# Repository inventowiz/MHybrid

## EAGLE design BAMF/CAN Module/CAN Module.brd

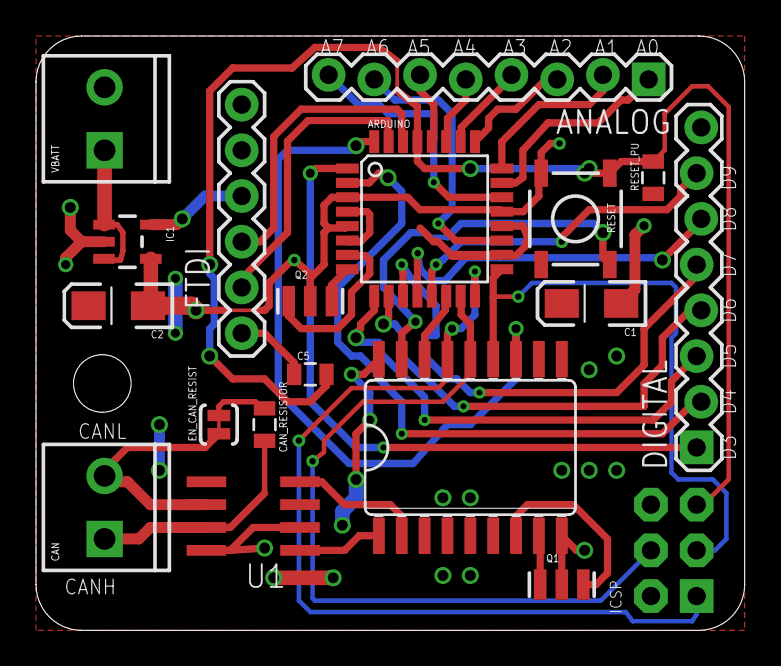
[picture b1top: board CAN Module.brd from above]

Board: 2 copper layers, 39.4 x 33.0 mm, 19 parts (0 on the bottom side), 37 nets.

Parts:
ANALOG: 1X08_LOCK
ARDUINO: TQFP32-08
C1, C2: 220uF; EIA3216-KIT
C5: .1uF; 0805
CAN: M023.5MM; SCREWTERMINAL-3.5MM-2
CAN_RESISTOR: 120; 0805
DIGITAL: 1X08_LOCK
EN_CAN_RESIST: SOLDERJUMPERTRACE; SJ_2S-TRACE
FTDI: FTDI_BASICPTH; FTDI_BASIC
IC1: SOT23-5
J1: AVR_SPI_PRG_6NS; 2X3-NS
Q1, Q2: 16MHz; RESONATOR-SMD
RESET: TACTILE_SWITCH_SMD
RESET_PU: 10k; 0805
U1: MCP2551-SN; SO-08
U$1: MCP2515SO; SO18L
VBATT: M023.5MM; SCREWTERMINAL-3.5MM-2

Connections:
5V: ARDUINO.4, ARDUINO.6, ARDUINO.18, ARDUINO.20, C1.A, C2.A, FTDI.VCC, IC1.5, J1.2, RESET_PU.1, U1.3, U$1.18
A0: ANALOG.1, ARDUINO.23
A1: ANALOG.2, ARDUINO.24
A2: ANALOG.3, ARDUINO.25
A3: ANALOG.4, ARDUINO.26
A4: ANALOG.5, ARDUINO.27
A5: ANALOG.6, ARDUINO.28
A6: ANALOG.7, ARDUINO.19
A7: ANALOG.8, ARDUINO.22
ARD_RX: ARDUINO.30, FTDI.TXO
ARD_TX: ARDUINO.31, FTDI.RXI
CANH: CAN.1, CAN_RESISTOR.2, U1.7
CANL: CAN.2, EN_CAN_RESIST.1, U1.6
CS: ARDUINO.14, U$1.16
D2: ARDUINO.32, U$1.12
D3: ARDUINO.1, DIGITAL.1
D4: ARDUINO.2, DIGITAL.2
D5: ARDUINO.9, DIGITAL.3
D6: ARDUINO.10, DIGITAL.4
D7: ARDUINO.11, DIGITAL.5
D8: ARDUINO.12, DIGITAL.6
D9: ARDUINO.13, DIGITAL.7
GND: ARDUINO.3, ARDUINO.5, ARDUINO.21, C1.C, C2.C, FTDI.GND, IC1.2, IC1.4, J1.6, Q1.2, Q2.2, RESET.3, U1.2, U1.8, U$1.9, VBATT.2
MISO: ARDUINO.16, J1.1, U$1.15
MOSI: ARDUINO.15, J1.4, U$1.14
unnamed: U1.4, U$1.2
unnamed: U1.1, U$1.1
unnamed: CAN_RESISTOR.1, EN_CAN_RESIST.2
unnamed: RESET.2, U$1.17
unnamed: ARDUINO.7, Q2.1
unnamed: ARDUINO.8, Q2.3
unnamed: C5.1, FTDI.DTR
unnamed: Q1.3, U$1.7
unnamed: Q1.1, U$1.8
unnamed: IC1.1, IC1.3, VBATT.1
RESET: ARDUINO.29, C5.2, J1.5, RESET.1, RESET_PU.2
SCK: ARDUINO.17, J1.3, U$1.13

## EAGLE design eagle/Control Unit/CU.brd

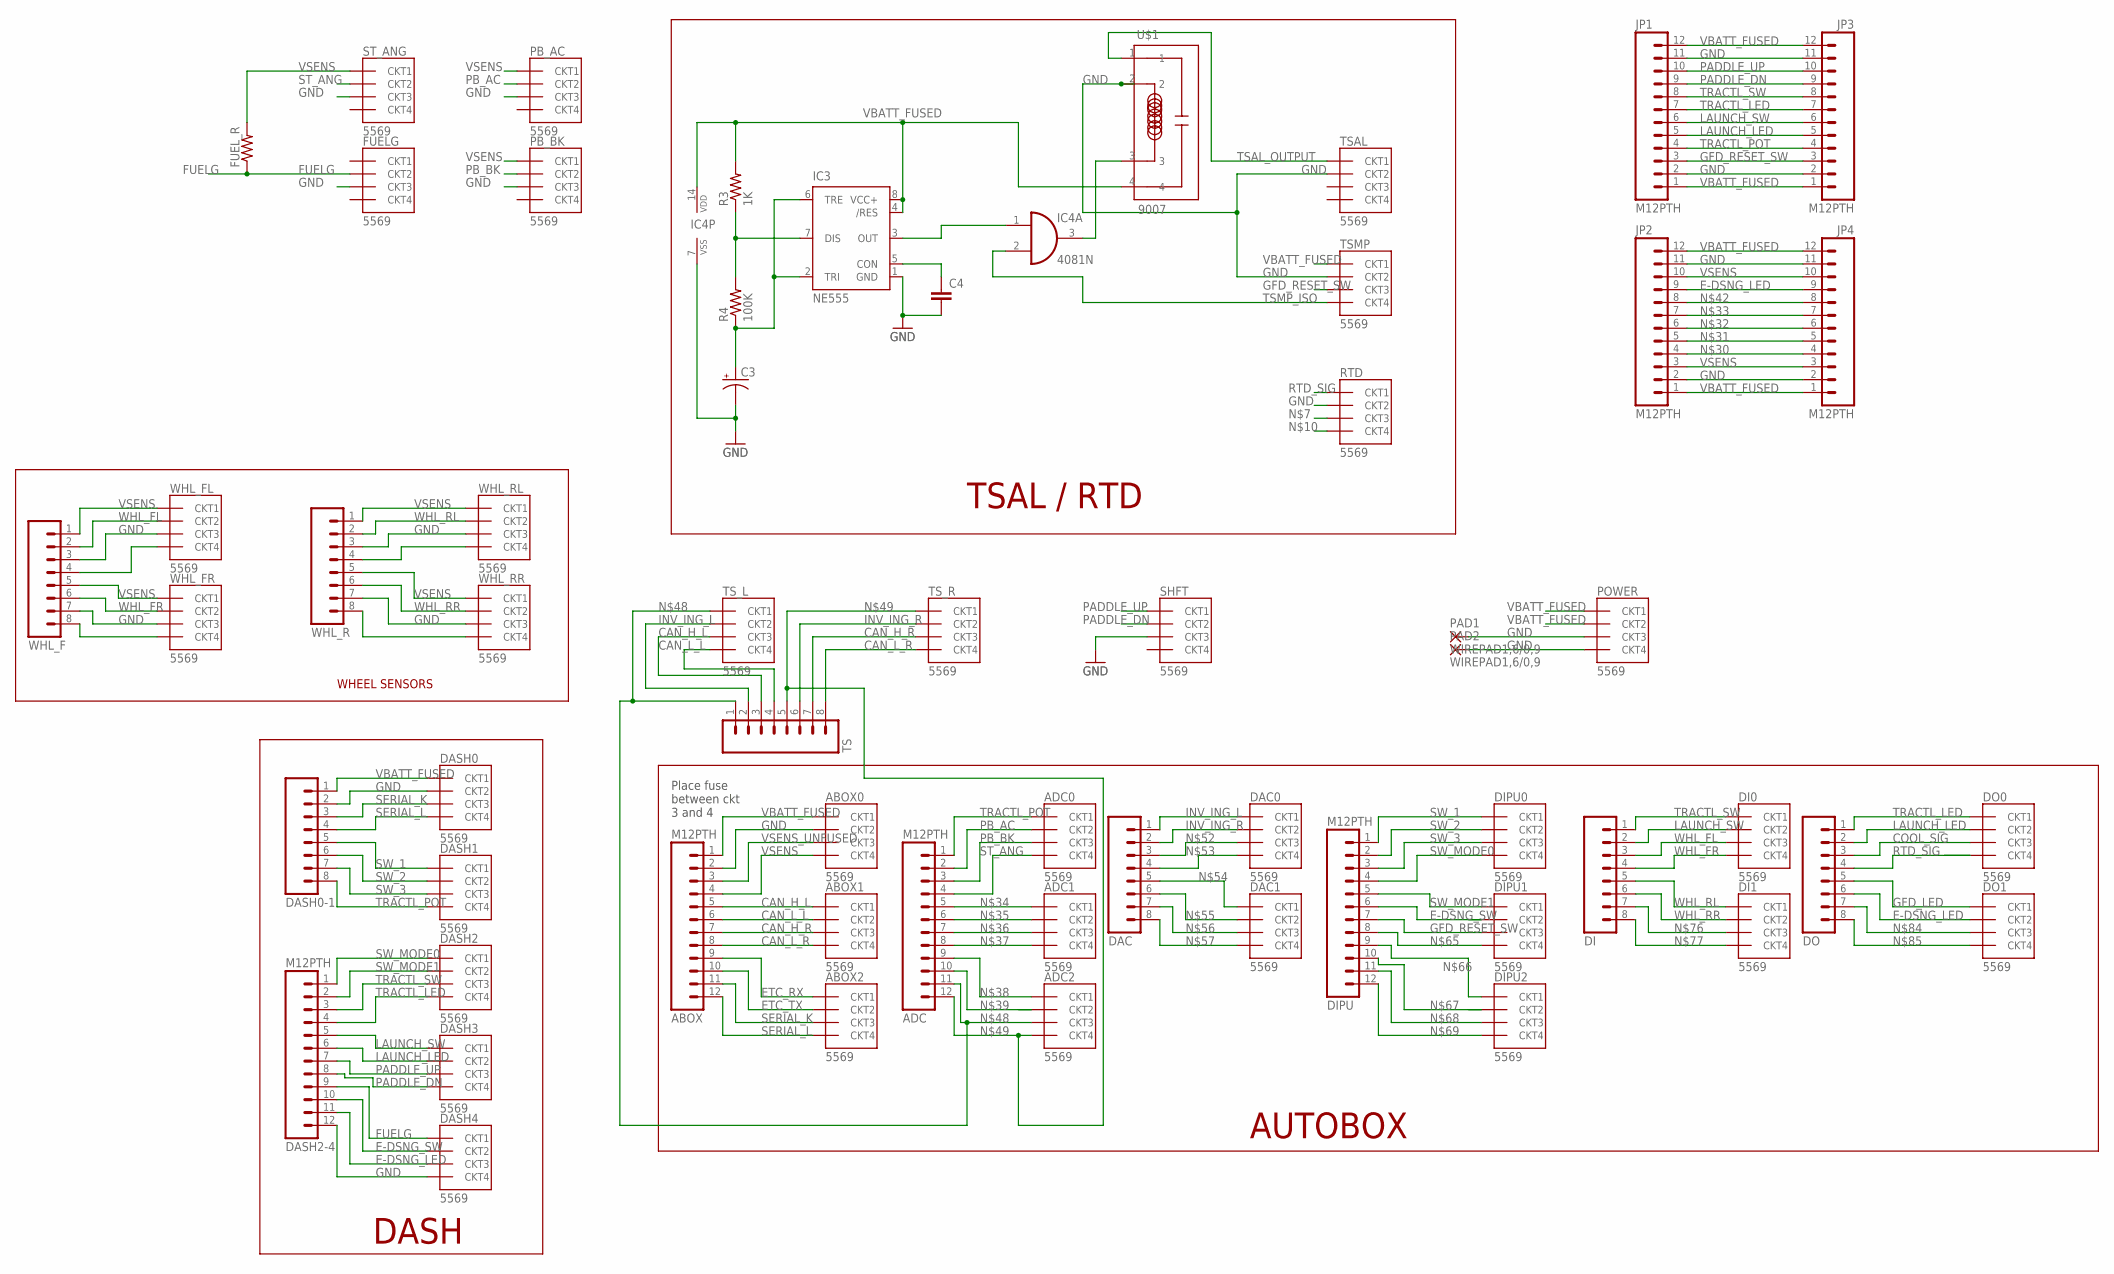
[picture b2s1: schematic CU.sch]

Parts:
ABOX: M12PTH; 1X12
ABOX0, ABOX1, ABOX2: 5569
ADC: M12PTH; 1X12
ADC0, ADC1, ADC2: 5569
C3: CAP_POLPTH1; CPOL-RADIAL-100UF-25V
C4: CAPPTH2; CAP-PTH-SMALL2
DAC: M081X08; 1X08
DAC0, DAC1: 5569
DASH0, DASH1, DASH2, DASH3, DASH4: 5569
DASH0-1: M081X08; 1X08
DASH2-4: M12PTH; 1X12
DI: M081X08; 1X08
DI0, DI1: 5569
DIPU: M12PTH; 1X12
DIPU0, DIPU1, DIPU2: 5569
DO: M081X08; 1X08
DO0, DO1: 5569
FUELG: 5569
FUEL_R: R-US_0204/7; 0204/7
IC3: NE555; DIL-08
IC4: 4081N; DIL14
JP1, JP2, JP3, JP4: M12PTH; 1X12
PAD1, PAD2: WIREPAD1,6/0,9; 1,6/0,9
PB_AC: 5569
PB_BK: 5569
POWER: 5569
R3: 1K; AXIAL-0.3EZ
R4: 100K; AXIAL-0.3EZ
RTD: 5569
SHFT: 5569
ST_ANG: 5569
TS: M081X08; 1X08
TSAL: 5569
TSMP: 5569
TS_L: 5569
TS_R: 5569
U$1: 9007
WHL_F: M081X08; 1X08
WHL_FL: 5569
WHL_FR: 5569
WHL_R: M081X08; 1X08
WHL_RL: 5569
WHL_RR: 5569

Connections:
CAN_H_L: ABOX.5, ABOX1.CKT1, TS.3, TS_L.CKT3
CAN_H_R: ABOX.7, ABOX1.CKT3, TS.7, TS_R.CKT3
CAN_L_L: ABOX.6, ABOX1.CKT2, TS.4, TS_L.CKT4
CAN_L_R: ABOX.8, ABOX1.CKT4, TS.8, TS_R.CKT4
COOL_SIG: DO.3, DO0.CKT3
E-DSNG_LED: DASH2-4.11, DASH4.CKT3, DO.6, DO1.CKT2, JP2.9, JP4.9
E-DSNG_SW: DASH2-4.10, DASH4.CKT2, DIPU.6, DIPU1.CKT2
ETC_RX: ABOX.9, ABOX2.CKT1
ETC_TX: ABOX.10, ABOX2.CKT2
FUELG: DASH2-4.9, DASH4.CKT1, FUELG.CKT2, FUEL_R.1
GFD_LED: DO.5, DO1.CKT1
GFD_RESET_SW: DIPU.7, DIPU1.CKT3, JP1.3, JP3.3, TSMP.CKT3
GND: ABOX.2, ABOX0.CKT2, C3.2 (-), C4.2, DASH0.CKT2, DASH0-1.2, DASH2-4.12, DASH4.CKT4, FUELG.CKT3, IC3.1 (GND), IC4.7 (VSS), JP1.2, JP1.11, JP2.2, JP2.11, JP3.2, JP3.11, JP4.2, JP4.11, PAD1.1, PAD2.1, PB_AC.CKT3, PB_BK.CKT3, POWER.CKT3, POWER.CKT4, RTD.CKT2, SHFT.CKT3, ST_ANG.CKT3, TSAL.CKT2, TSMP.CKT2, U$1.2, WHL_F.3, WHL_F.7, WHL_FL.CKT3, WHL_FR.CKT3, WHL_R.3, WHL_R.7, WHL_RL.CKT3, WHL_RR.CKT3
INV_ING_L: DAC.1, DAC0.CKT1, TS.2, TS_L.CKT2
INV_ING_R: DAC.2, DAC0.CKT2, TS.6, TS_R.CKT2
LAUNCH_LED: DASH2-4.6, DASH3.CKT2, DO.2, DO0.CKT2, JP1.5, JP3.5
LAUNCH_SW: DASH2-4.5, DASH3.CKT1, DI.2, DI0.CKT2, JP1.6, JP3.6
unnamed: WHL_F.4, WHL_FL.CKT4
unnamed: WHL_F.8, WHL_FR.CKT4
unnamed: WHL_R.8, WHL_RR.CKT4
unnamed: IC3.3 (OUT), IC4.1 (I0)
unnamed: WHL_R.4, WHL_RL.CKT4
unnamed: IC4.3 (O), U$1.3
unnamed: IC3.7 (DIS), R3.P$1 (1), R4.P$2 (2)
unnamed: C3.1 (+), IC3.2 (TRI), IC3.6 (TRE), R4.P$1 (1)
unnamed: C4.1, IC3.5 (CON)
unnamed: JP2.4, JP4.4
unnamed: JP2.5, JP4.5
unnamed: JP2.6, JP4.6
unnamed: JP2.7, JP4.7
unnamed: ADC.5, ADC1.CKT1
unnamed: ADC.6, ADC1.CKT2
unnamed: ADC.7, ADC1.CKT3
unnamed: ADC.8, ADC1.CKT4
unnamed: ADC.9, ADC2.CKT1
unnamed: ADC.10, ADC2.CKT2
unnamed: JP2.8, JP4.8
unnamed: ADC.11, ADC2.CKT3, TS.1, TS_L.CKT1
unnamed: ADC.12, ADC2.CKT4, TS.5, TS_R.CKT1
unnamed: DAC.3, DAC0.CKT3
unnamed: DAC.4, DAC0.CKT4
unnamed: DAC.5, DAC1.CKT1
unnamed: DAC.6, DAC1.CKT2
unnamed: DAC.7, DAC1.CKT3
unnamed: DAC.8, DAC1.CKT4
unnamed: DIPU.8, DIPU1.CKT4
unnamed: DIPU.9, DIPU2.CKT1
unnamed: DIPU.10, DIPU2.CKT2
unnamed: DIPU.11, DIPU2.CKT3
unnamed: DIPU.12, DIPU2.CKT4
unnamed: DI.7, DI1.CKT3
unnamed: DI.8, DI1.CKT4
unnamed: DO.7, DO1.CKT3
unnamed: DO.8, DO1.CKT4
PADDLE_DN: DASH2-4.8, DASH3.CKT4, JP1.9, JP3.9, SHFT.CKT2
PADDLE_UP: DASH2-4.7, DASH3.CKT3, JP1.10, JP3.10, SHFT.CKT1
PB_AC: ADC.2, ADC0.CKT2, PB_AC.CKT2
PB_BK: ADC.3, ADC0.CKT3, PB_BK.CKT2
RTD_SIG: DO.4, DO0.CKT4, RTD.CKT1
SERIAL_K: ABOX.11, ABOX2.CKT3, DASH0.CKT3, DASH0-1.3
SERIAL_L: ABOX.12, ABOX2.CKT4, DASH0.CKT4, DASH0-1.4
ST_ANG: ADC.4, ADC0.CKT4, ST_ANG.CKT2
SW_1: DASH0-1.5, DASH1.CKT1, DIPU.1, DIPU0.CKT1
SW_2: DASH0-1.6, DASH1.CKT2, DIPU.2, DIPU0.CKT2
SW_3: DASH0-1.7, DASH1.CKT3, DIPU.3, DIPU0.CKT3
SW_MODE0: DASH2.CKT1, DASH2-4.1, DIPU.4, DIPU0.CKT4
SW_MODE1: DASH2.CKT2, DASH2-4.2, DIPU.5, DIPU1.CKT1
TRACTL_LED: DASH2.CKT4, DASH2-4.4, DO.1, DO0.CKT1, JP1.7, JP3.7
TRACTL_POT: ADC.1, ADC0.CKT1, DASH0-1.8, DASH1.CKT4, JP1.4, JP3.4
TRACTL_SW: DASH2.CKT3, DASH2-4.3, DI.1, DI0.CKT1, JP1.8, JP3.8
TSAL_OUTPUT: TSAL.CKT1, U$1.1
TSMP_ISO: IC4.2 (I1), TSMP.CKT4
VBATT_FUSED: ABOX.1, ABOX0.CKT1, DASH0.CKT1, DASH0-1.1, IC3.4 (/RES), IC3.8 (VCC+), IC4.14 (VDD), JP1.1, JP1.12, JP2.1, JP2.12, JP3.1, JP3.12, JP4.1, JP4.12, POWER.CKT1, POWER.CKT2, R3.P$2 (2), TSMP.CKT1, U$1.4
VSENS: ABOX.4, ABOX0.CKT4, FUEL_R.2, JP2.3, JP2.10, JP4.3, JP4.10, PB_AC.CKT1, PB_BK.CKT1, ST_ANG.CKT1, WHL_F.1, WHL_F.5, WHL_FL.CKT1, WHL_FR.CKT1, WHL_R.1, WHL_R.5, WHL_RL.CKT1, WHL_RR.CKT1
VSENS_UNFUSED: ABOX.3, ABOX0.CKT3
WHL_FL: DI.3, DI0.CKT3, WHL_F.2, WHL_FL.CKT2
WHL_FR: DI.4, DI0.CKT4, WHL_F.6, WHL_FR.CKT2
WHL_RL: DI.5, DI1.CKT1, WHL_R.2, WHL_RL.CKT2
WHL_RR: DI.6, DI1.CKT2, WHL_R.6, WHL_RR.CKT2

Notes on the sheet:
WHEEL SENSORS
TSAL / RTD
AUTOBOX
DASH
Place fuse between ckt 3 and 4

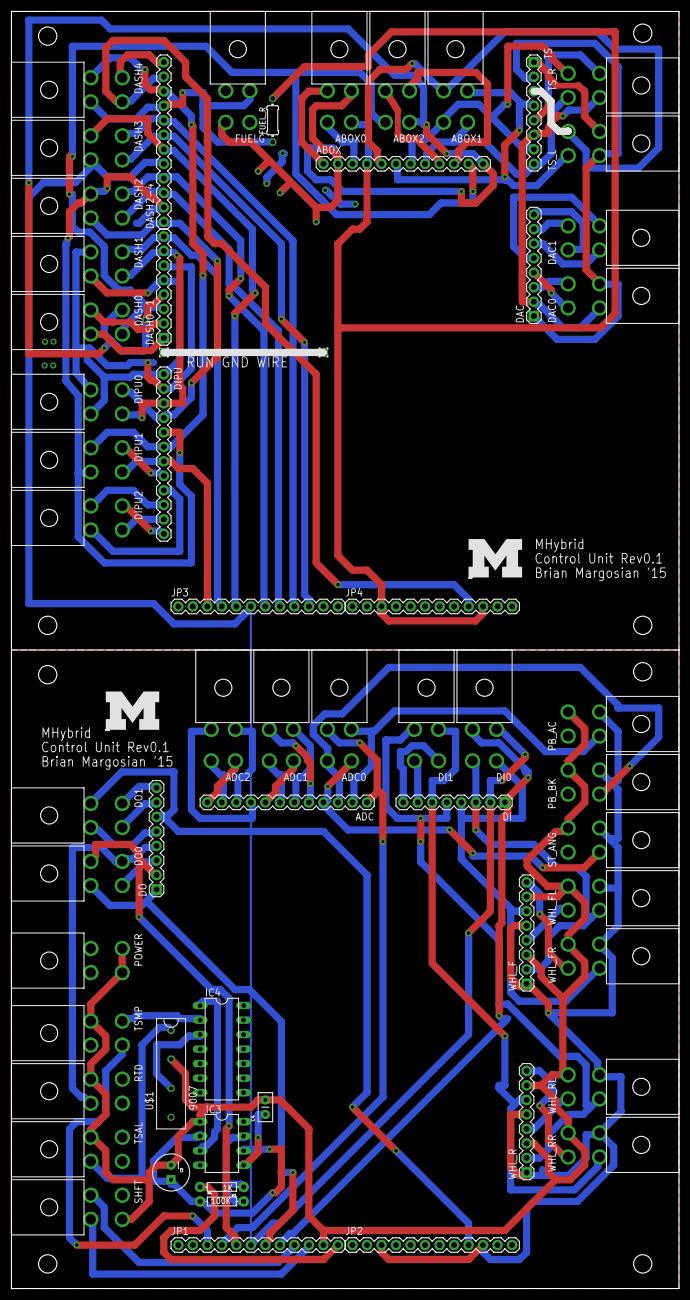
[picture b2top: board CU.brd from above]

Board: 3 copper layers, 116.8 x 223.5 mm, 62 parts (0 on the bottom side), 79 nets.

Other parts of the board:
U$2, U$3: BLOCKM

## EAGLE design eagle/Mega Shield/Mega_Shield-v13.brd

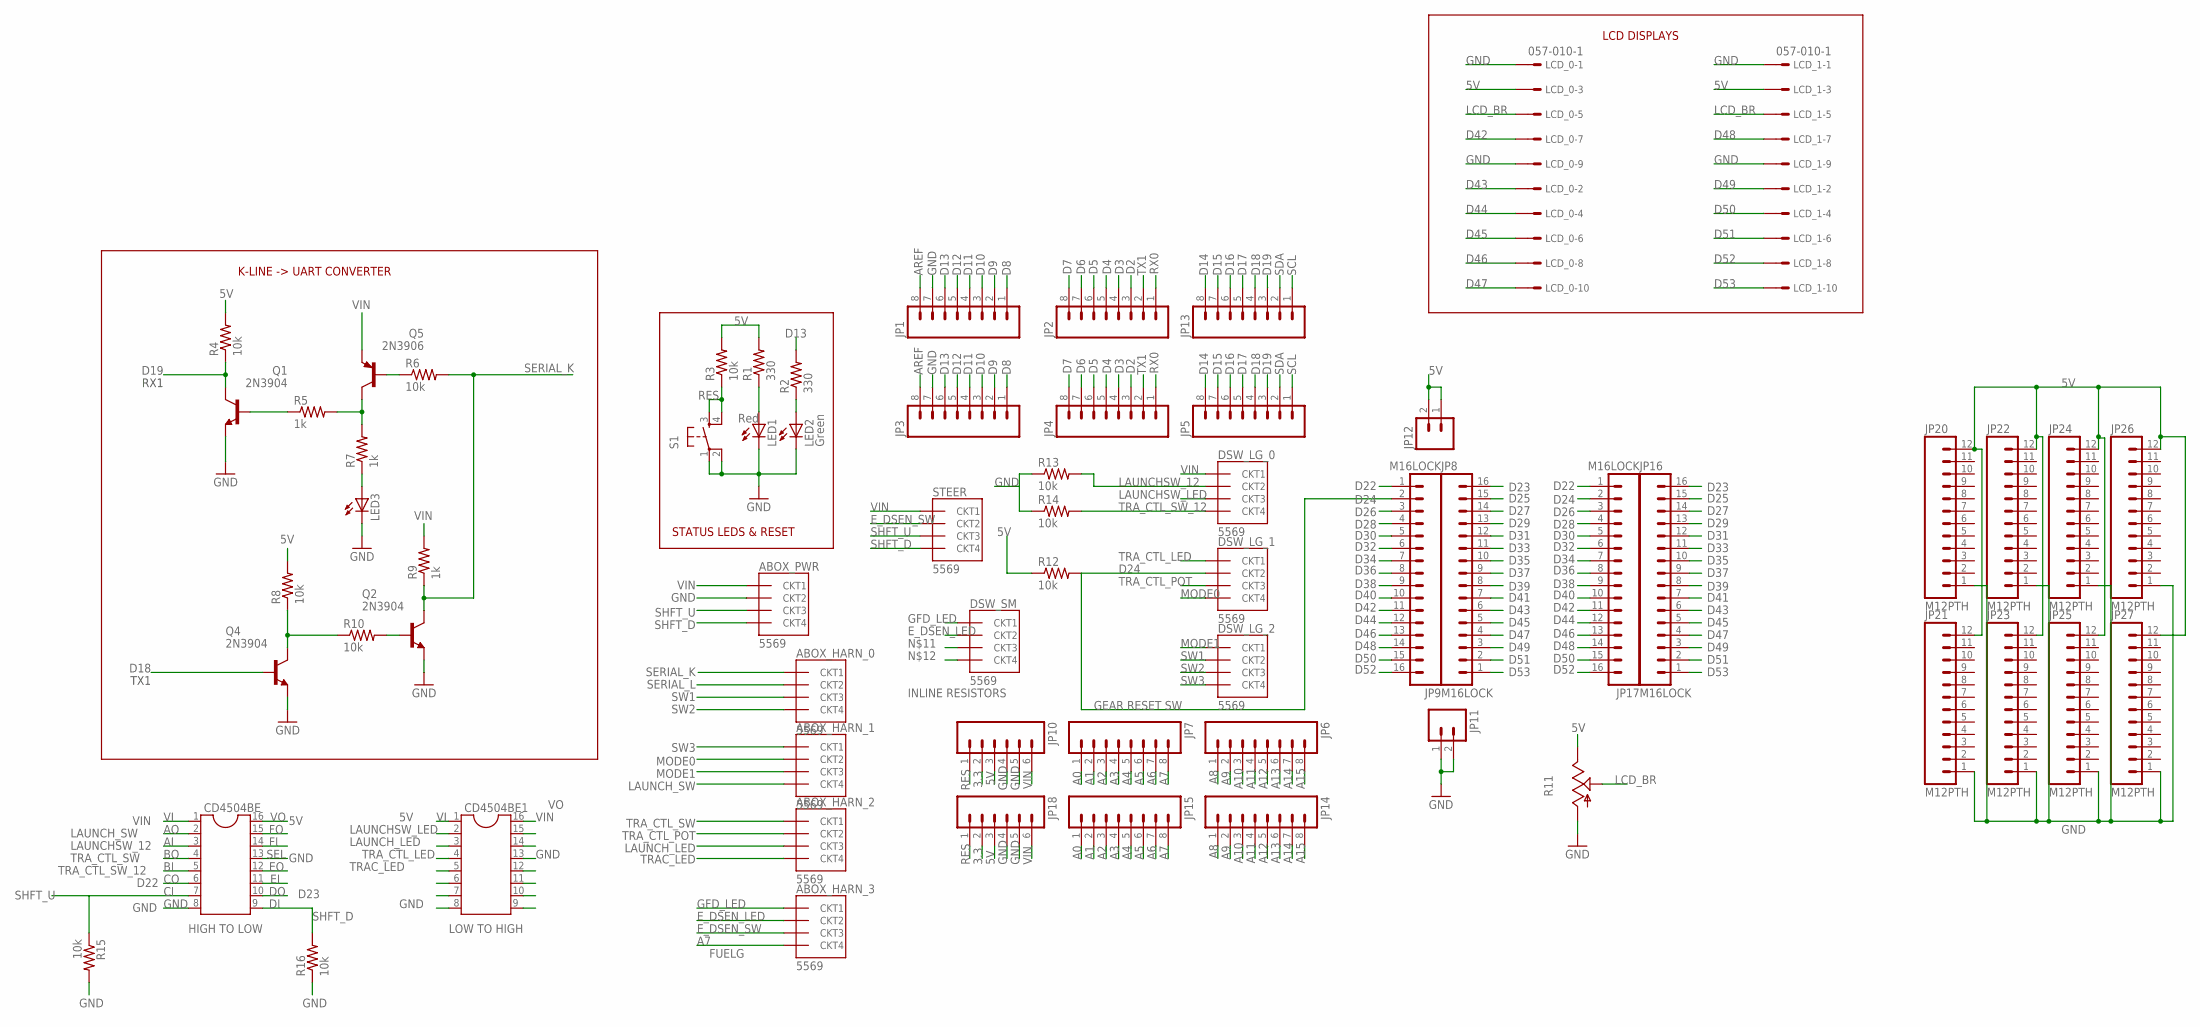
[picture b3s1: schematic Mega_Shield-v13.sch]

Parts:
ABOX_HARN_0, ABOX_HARN_1, ABOX_HARN_2, ABOX_HARN_3: 5569
ABOX_PWR: 5569
CD4504BE, CD4504BE1: DIL16S; SOCKET-16
DSW_LG_0, DSW_LG_1, DSW_LG_2: 5569
DSW_SM: 5569
JP1, JP2, JP3, JP4, JP5, JP6, JP7, JP13, JP14, JP15: M08LOCK; 1X08_LOCK
JP8, JP9, JP16, JP17: M16LOCK; 1X16_LOCK
JP10, JP18: M06LOCK; 1X06_LOCK
JP11, JP12: M02LOCK; 1X02_LOCK
JP20, JP21, JP22, JP23, JP24, JP25, JP26, JP27: M12PTH; 1X12
LCD_0, LCD_1: 057-010-1
LED1: Red; LED5MM
LED2: Green; LED5MM
LED3: LED5MM
Q1, Q2, Q4: 2N3904; TO92
Q5: 2N3906; TO92
R1, R2: 330; AXIAL-0.3
R3: 10k; AXIAL-0.3
R4, R6, R8, R10, R12, R13, R14, R15, R16: 10k; AXIAL-0.3EZ
R5, R7, R9: 1k; AXIAL-0.3EZ
R11: TRIM_US-CT6; CT6
S1: TAC_SWITCHPTH; TACTILE-PTH
STEER: 5569

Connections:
3.3: JP10.2, JP18.2
5V: CD4504BE.16, CD4504BE1.1, JP10.3, JP12.1, JP12.2, JP18.3, JP20.12, JP21.12, JP22.12, JP23.12, JP24.12, JP25.12, JP26.12, JP27.12, LCD_0.3, LCD_1.3, R1.P$2 (2), R3.P$2 (2), R4.P$2 (2), R8.P$2 (2), R11.E, R12.P$1 (1)
A0: JP7.1, JP15.1
A1: JP7.2, JP15.2
A2: JP7.3, JP15.3
A3: JP7.4, JP15.4
A4: JP7.5, JP15.5
A5: JP7.6, JP15.6
A6: JP7.7, JP15.7
A7: ABOX_HARN_3.CKT4, JP7.8, JP15.8
A8: JP6.1, JP14.1
A9: JP6.2, JP14.2
A10: JP6.3, JP14.3
A11: JP6.4, JP14.4
A12: JP6.5, JP14.5
A13: JP6.6, JP14.6
A14: JP6.7, JP14.7
A15: JP6.8, JP14.8
AREF: JP1.8, JP3.8
D2: JP2.3, JP4.3
D3: JP2.4, JP4.4
D4: JP2.5, JP4.5
D5: JP2.6, JP4.6
D6: JP2.7, JP4.7
D7: JP2.8, JP4.8
D8: JP1.1, JP3.1
D9: JP1.2, JP3.2
D10: JP1.3, JP3.3
D11: JP1.4, JP3.4
D12: JP1.5, JP3.5
D13: JP1.6, JP3.6, R2.P$2 (2)
D14: JP5.8, JP13.8
D15: JP5.7, JP13.7
D16: JP5.6, JP13.6
D17: JP5.5, JP13.5
D18: JP5.4, JP13.4, Q4.2 (B)
D19: JP5.3, JP13.3, Q1.1 (C), R4.P$1 (1)
D22: CD4504BE.6, JP9.1, JP17.1
D23: CD4504BE.10, JP8.16, JP16.16
D24: DSW_LG_1.CKT2, JP9.2, JP17.2, R12.P$2 (2)
D25: JP8.15, JP16.15
D26: JP9.3, JP17.3
D27: JP8.14, JP16.14
D28: JP9.4, JP17.4
D29: JP8.13, JP16.13
D30: JP9.5, JP17.5
D31: JP8.12, JP16.12
D32: JP9.6, JP17.6
D33: JP8.11, JP16.11
D34: JP9.7, JP17.7
D35: JP8.10, JP16.10
D36: JP9.8, JP17.8
D37: JP8.9, JP16.9
D38: JP9.9, JP17.9
D39: JP8.8, JP16.8
D40: JP9.10, JP17.10
D41: JP8.7, JP16.7
D42: JP9.11, JP17.11, LCD_0.7
D43: JP8.6, JP16.6, LCD_0.2
D44: JP9.12, JP17.12, LCD_0.4
D45: JP8.5, JP16.5, LCD_0.6
D46: JP9.13, JP17.13, LCD_0.8
D47: JP8.4, JP16.4, LCD_0.10
D48: JP9.14, JP17.14, LCD_1.7
D49: JP8.3, JP16.3, LCD_1.2
D50: JP9.15, JP17.15, LCD_1.4
D51: JP8.2, JP16.2, LCD_1.6
D52: JP9.16, JP17.16, LCD_1.8
D53: JP8.1, JP16.1, LCD_1.10
E_DSEN_LED: ABOX_HARN_3.CKT2, DSW_SM.CKT2
E_DSEN_SW: ABOX_HARN_3.CKT3, STEER.CKT2
GFD_LED: ABOX_HARN_3.CKT1, DSW_SM.CKT1
GND: ABOX_PWR.CKT2, CD4504BE.8, CD4504BE.13, CD4504BE1.8, CD4504BE1.13, JP1.7, JP3.7, JP10.4, JP10.5, JP11.1, JP11.2, JP18.4, JP18.5, JP20.1, JP21.1, JP22.1, JP23.1, JP24.1, JP25.1, JP26.1, JP27.1, LCD_0.1, LCD_0.9, LCD_1.1, LCD_1.9, LED1.K (C), LED2.K (C), LED3.K (C), Q1.3 (E), Q2.3 (E), Q4.3 (E), R11.A, R13.P$1 (1), R14.P$1 (1), R15.P$2 (2), R16.P$1 (1), S1.1, S1.2
LAUNCHSW_12: CD4504BE.3, DSW_LG_0.CKT2, R13.P$2 (2)
LAUNCHSW_LED: CD4504BE1.2, DSW_LG_0.CKT3
LAUNCH_LED: ABOX_HARN_2.CKT3, CD4504BE1.3
LAUNCH_SW: ABOX_HARN_1.CKT4, CD4504BE.2
LCD_BR: LCD_0.5, LCD_1.5, R11.S
MODE0: ABOX_HARN_1.CKT2, DSW_LG_1.CKT4
MODE1: ABOX_HARN_1.CKT3, DSW_LG_2.CKT1
unnamed: Q1.2 (B), R5.P$1 (1)
unnamed: Q5.1 (C), R5.P$2 (2), R7.P$2 (2)
unnamed: Q5.2 (B), R6.P$1 (1)
unnamed: LED3.A, R7.P$1 (1)
unnamed: Q2.2 (B), R10.P$2 (2)
unnamed: Q4.1 (C), R8.P$1 (1), R10.P$1 (1)
unnamed: LED1.A, R1.P$1 (1)
unnamed: LED2.A, R2.P$1 (1)
RES: JP10.1, JP18.1, R3.P$1 (1), S1.3, S1.4
RX0: JP2.1, JP4.1
SCL: JP5.1, JP13.1
SDA: JP5.2, JP13.2
SERIAL_K: ABOX_HARN_0.CKT1, Q2.1 (C), R6.P$2 (2), R9.P$1 (1)
SERIAL_L: ABOX_HARN_0.CKT2
SHFT_D: ABOX_PWR.CKT4, CD4504BE.9, R16.P$2 (2), STEER.CKT4
SHFT_U: ABOX_PWR.CKT3, CD4504BE.7, R15.P$1 (1), STEER.CKT3
SW1: ABOX_HARN_0.CKT3, DSW_LG_2.CKT2
SW2: ABOX_HARN_0.CKT4, DSW_LG_2.CKT3
SW3: ABOX_HARN_1.CKT1, DSW_LG_2.CKT4
TRAC_LED: ABOX_HARN_2.CKT4, CD4504BE1.5
TRA_CTL_LED: CD4504BE1.4, DSW_LG_1.CKT1
TRA_CTL_POT: ABOX_HARN_2.CKT2, DSW_LG_1.CKT3
TRA_CTL_SW: ABOX_HARN_2.CKT1, CD4504BE.4
TRA_CTL_SW_12: CD4504BE.5, DSW_LG_0.CKT4, R14.P$2 (2)
TX1: JP2.2, JP4.2
VIN: ABOX_PWR.CKT1, CD4504BE.1, CD4504BE1.16, DSW_LG_0.CKT1, JP10.6, JP18.6, Q5.3 (E), R9.P$2 (2), STEER.CKT1

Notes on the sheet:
STATUS LEDS & RESET
RX1
TX1
K-LINE -> UART CONVERTER
LCD DISPLAYS
GND
SEL
HIGH TO LOW
LOW TO HIGH
GEAR RESET SW
INLINE RESISTORS
FUELG

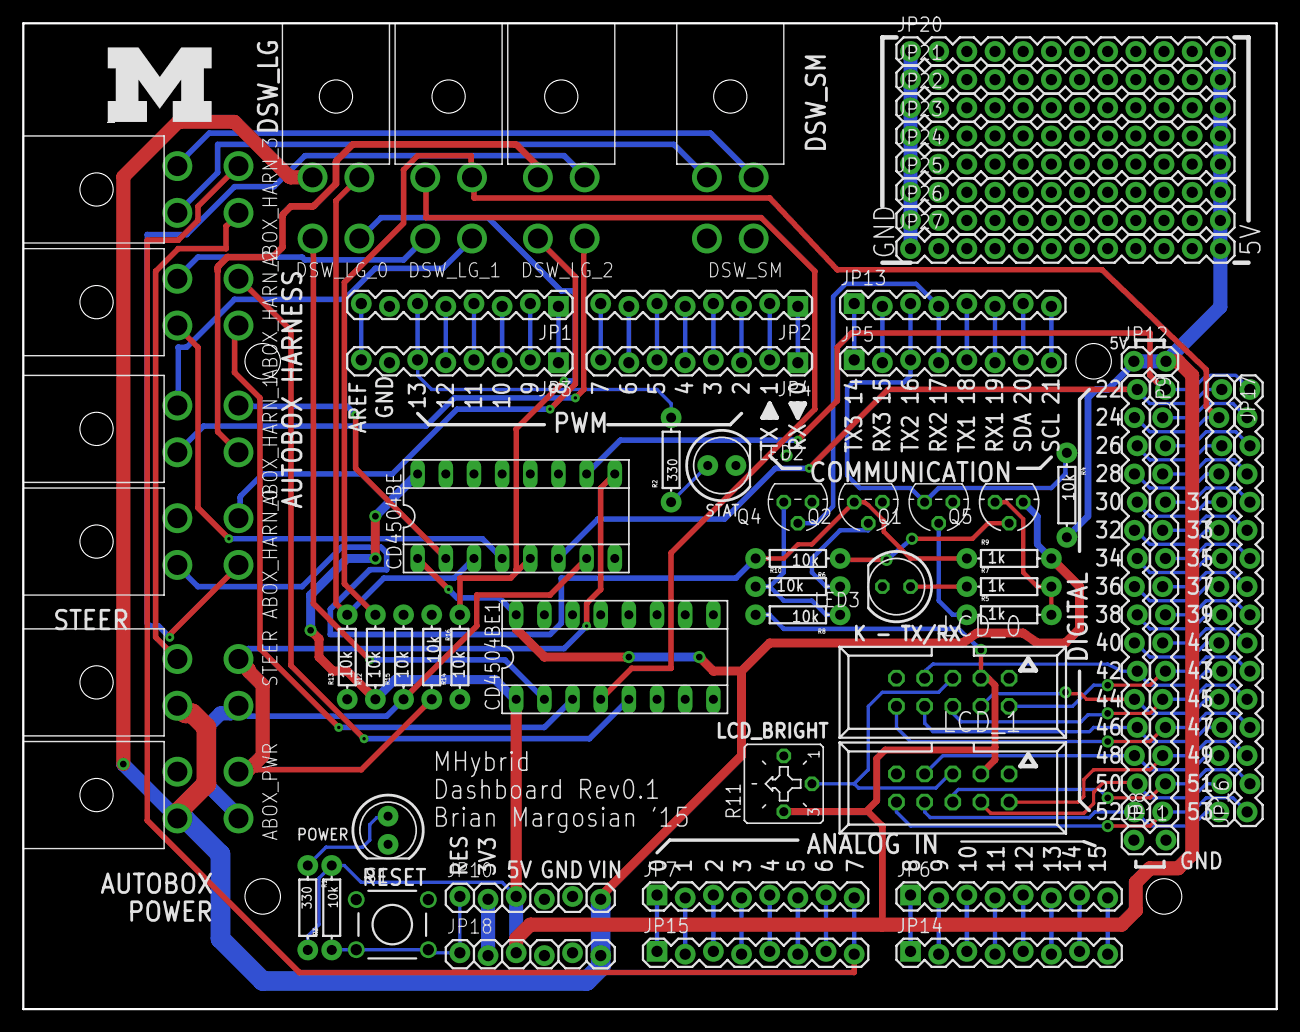
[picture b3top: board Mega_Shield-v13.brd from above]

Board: 2 copper layers, 113.0 x 88.9 mm, 65 parts (0 on the bottom side), 105 nets.

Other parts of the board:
U$1: BLOCKM

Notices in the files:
parts and their libraries:
SparkFun-DigitalIC: Licensing: CC v3.0 Share-Alike You are welcome to use this library for commercial purposes.
